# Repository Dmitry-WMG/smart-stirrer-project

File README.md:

# smart-stirrer-project
Unzip/copy this folder into the examples/ble_peripheral/ folder in the nRF SDK v.16.
Copy the stirboard.h file into components/boards folder.

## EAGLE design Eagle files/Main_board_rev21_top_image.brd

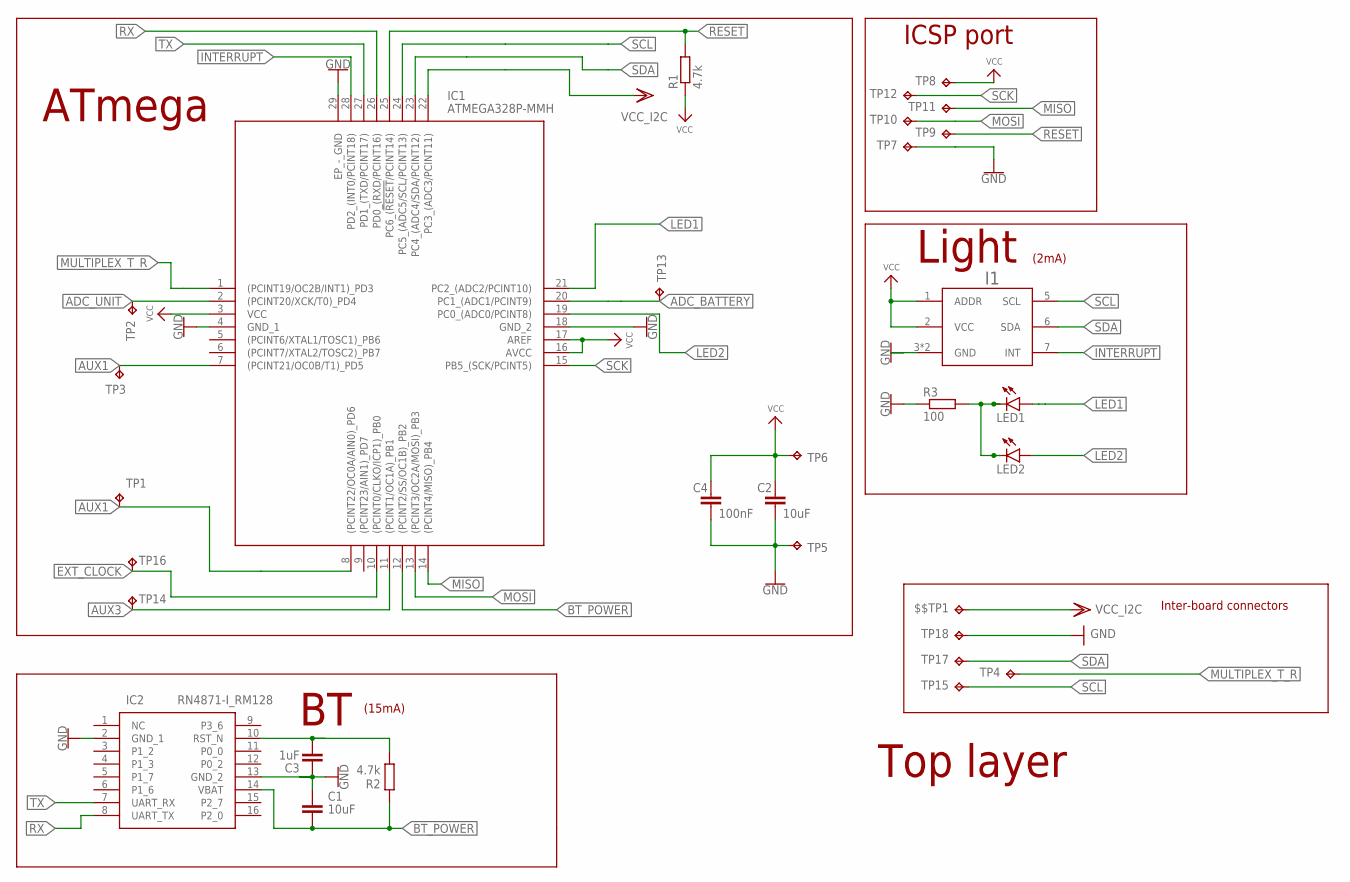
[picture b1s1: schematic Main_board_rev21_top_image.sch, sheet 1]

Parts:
$$TP1: TP; TEST_PAD_1MM
C1, C2: 10uF; C0603K
C3: 1uF; C0603K
C4: 100nF; C0603K
I1: BH1745NUC; WSON008X2120
IC1: ATMEGA328P-MMH; QFN45P400X400X100-29N
IC2: RN4871-I_RM128; RN4871
LED1, LED2: LEDCHIPLED_0603; CHIPLED_0603
R1, R2: 4.7k; R0603
R3: 100; R0603
TP1, TP2, TP3, TP4, TP5, TP6, TP13, TP14, TP15, TP16, TP17, TP18: TP; TEST_PAD_1MM
TP7, TP8, TP9, TP10, TP11, TP12: TPTP09SQ; TP09SQ

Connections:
ADC_BATTERY: IC1.20 (PC1_(ADC1/PCINT9)), TP13.P$1
ADC_UNIT: IC1.2 ((PCINT20/XCK/T0)_PD4), TP2.P$1
AUX1: IC1.7 ((PCINT21/OC0B/T1)_PD5), TP3.P$1
AUX3: IC1.11 ((PCINT1/OC1A)_PB1), TP14.P$1
BT_POWER: C1.1, IC1.12 ((PCINT2/SS/OC1B)_PB2), IC2.14 (VBAT), R2.2
BT_RESET: C3.2, IC2.10 (RST_N), R2.1
EXT_CLOCK: IC1.10 ((PCINT0/CLKO/ICP1)_PB0), TP16.P$1
GND: C1.2, C2.2, C3.1, C4.2, I1.3 (GND), I1.4 (GND), IC1.4 (GND_1), IC1.18 (GND_2), IC1.29 (EP_-_GND), IC2.2 (GND_1), IC2.13 (GND_2), R3.1, TP5.P$1, TP7.TP, TP18.P$1
INTERRUPT: I1.7 (INT), IC1.28 (PD2_(INT0/PCINT18))
LED1: IC1.21 (PC2_(ADC2/PCINT10)), LED1.A
LED2: IC1.19 (PC0_(ADC0/PCINT8)), LED2.A
MISO: IC1.14 ((PCINT4/MISO)_PB4), TP11.TP
MOSI: IC1.13 ((PCINT3/OC2A/MOSI)_PB3), TP10.TP
MULTIPLEX_T_R: IC1.1 ((PCINT19/OC2B/INT1)_PD3), TP4.P$1
unnamed: IC1.8 ((PCINT22/OC0A/AIN0)_PD6), TP1.P$1
unnamed: LED1.C, LED2.C, R3.2
RESET: IC1.25 (PC6_(!RESET!/PCINT14)), R1.2, TP9.TP
RX: IC1.26 (PD0_(RXD/PCINT16)), IC2.8 (UART_TX)
SCK: IC1.15 (PB5_(SCK/PCINT5)), TP12.TP
SCL: I1.5 (SCL), IC1.24 (PC5_(ADC5/SCL/PCINT13)), TP15.P$1
SDA: I1.6 (SDA), IC1.23 (PC4_(ADC4/SDA/PCINT12)), TP17.P$1
TX: IC1.27 (PD1_(TXD/PCINT17)), IC2.7 (UART_RX)
VCC: C2.1, C4.1, I1.1 (ADDR), I1.2 (VCC), IC1.3 (VCC), IC1.16 (AVCC), IC1.17 (AREF), R1.1, TP6.P$1, TP8.TP
VDD: $$TP1.P$1, IC1.22 (PC3_(ADC3/PCINT11))

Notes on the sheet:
ICSP port
Light
ATmega
(2mA)
(15mA)
Top layer
Inter-board connectors

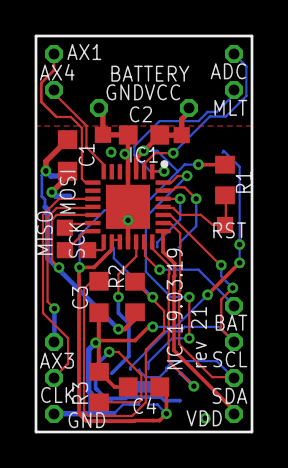
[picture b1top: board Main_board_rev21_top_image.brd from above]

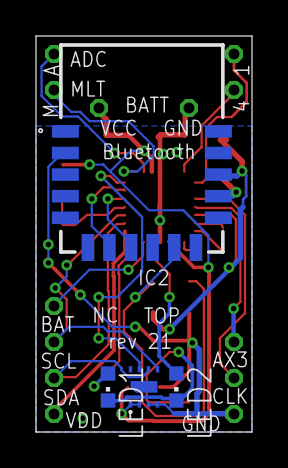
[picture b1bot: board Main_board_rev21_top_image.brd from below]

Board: 2 copper layers, 12.0 x 22.0 mm, 31 parts (4 on the bottom side), 24 nets.

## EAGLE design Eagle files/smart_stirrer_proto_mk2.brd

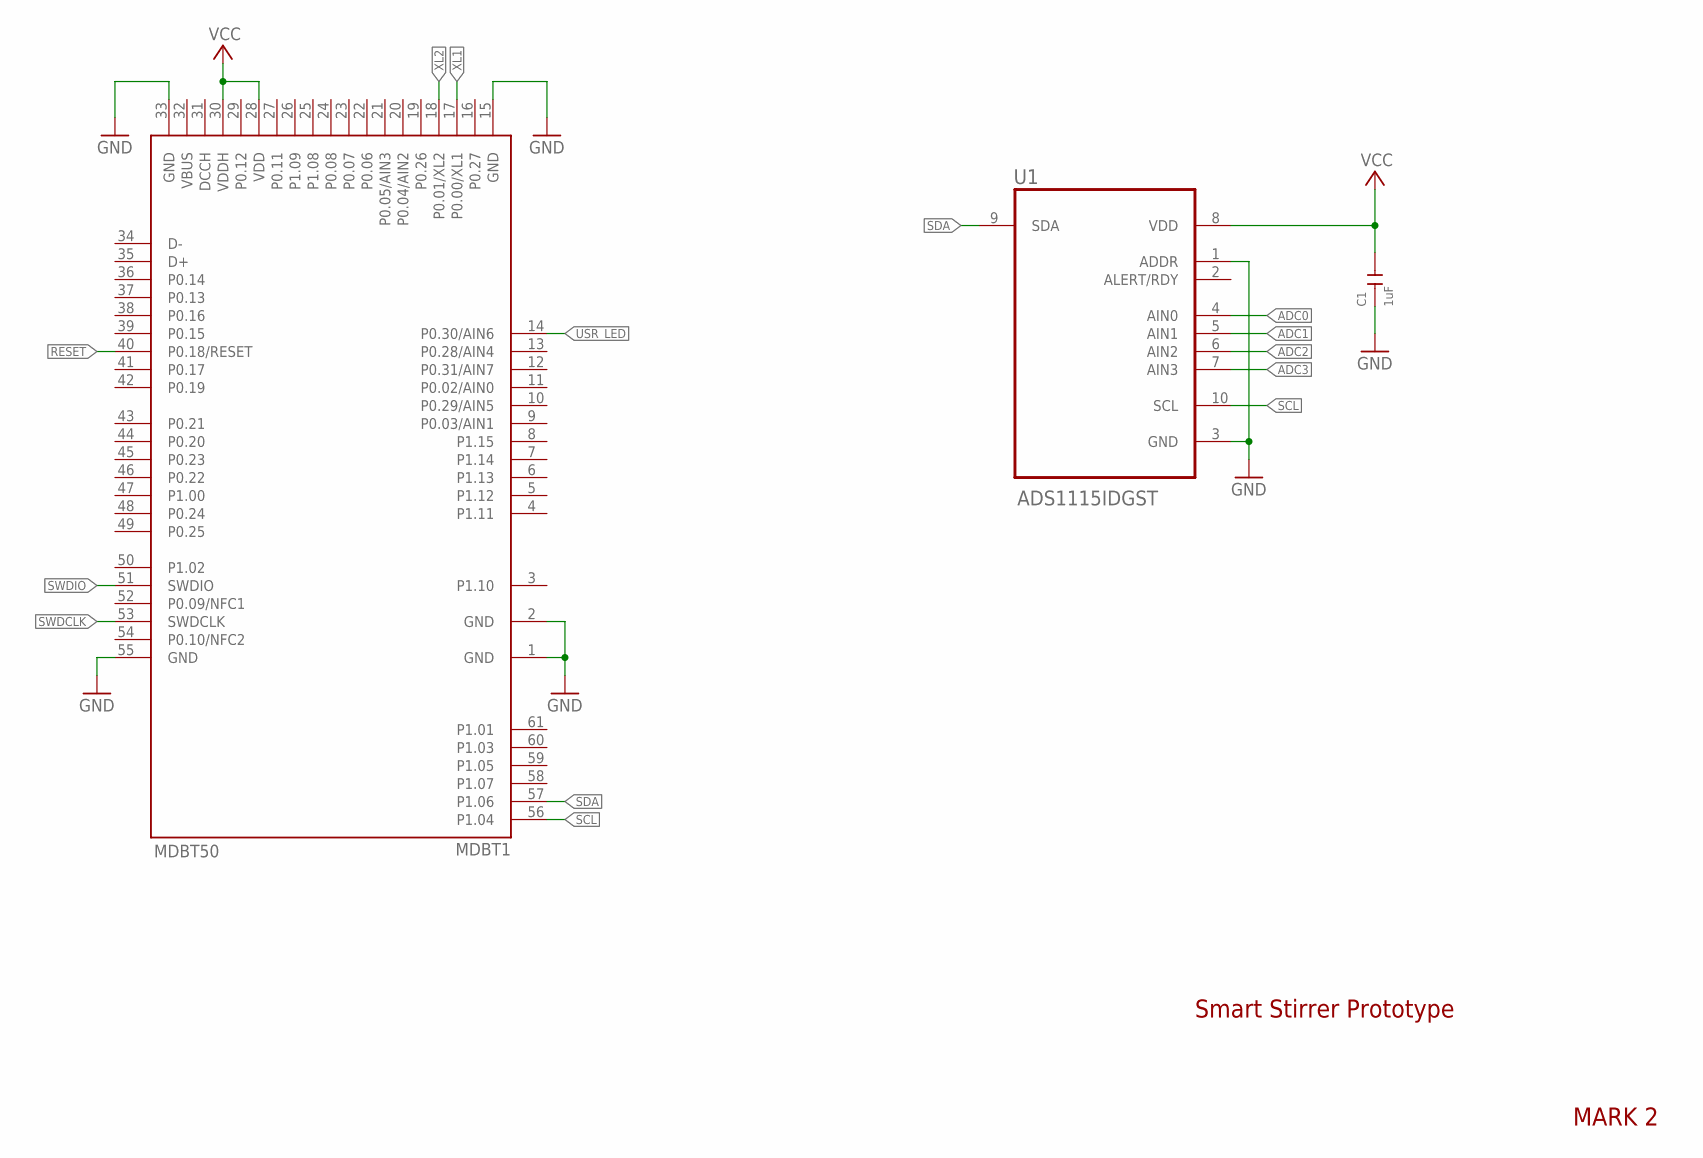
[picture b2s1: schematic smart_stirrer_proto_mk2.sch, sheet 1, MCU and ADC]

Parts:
C1: 1uF; C0402
MDBT1: MDBT50
U1: ADS1115IDGST; SOP50P490X110-10N

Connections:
ADC0: U1.4 (AIN0); also elsewhere on the board
ADC1: U1.5 (AIN1); also elsewhere on the board
ADC2: U1.6 (AIN2); also elsewhere on the board
ADC3: U1.7 (AIN3)
GND: C1.1, MDBT1.1 (GND), MDBT1.2 (GND), MDBT1.15 (GND), MDBT1.33 (GND), MDBT1.55 (GND), U1.1 (ADDR), U1.3 (GND); also elsewhere on the board
RESET: MDBT1.40 (P0.18/RESET); also elsewhere on the board
SCL: MDBT1.56 (P1.04), U1.10 (SCL); also elsewhere on the board
SDA: MDBT1.57 (P1.06), U1.9 (SDA); also elsewhere on the board
SWDCLK: MDBT1.53 (SWDCLK); also elsewhere on the board
SWDIO: MDBT1.51 (SWDIO); also elsewhere on the board
USR_LED: MDBT1.14 (P0.30/AIN6); also elsewhere on the board
VCC: C1.2, MDBT1.28 (VDD), MDBT1.30 (VDDH), U1.8 (VDD); also elsewhere on the board
XL1: MDBT1.17 (P0.00/XL1); also elsewhere on the board
XL2: MDBT1.18 (P0.01/XL2); also elsewhere on the board

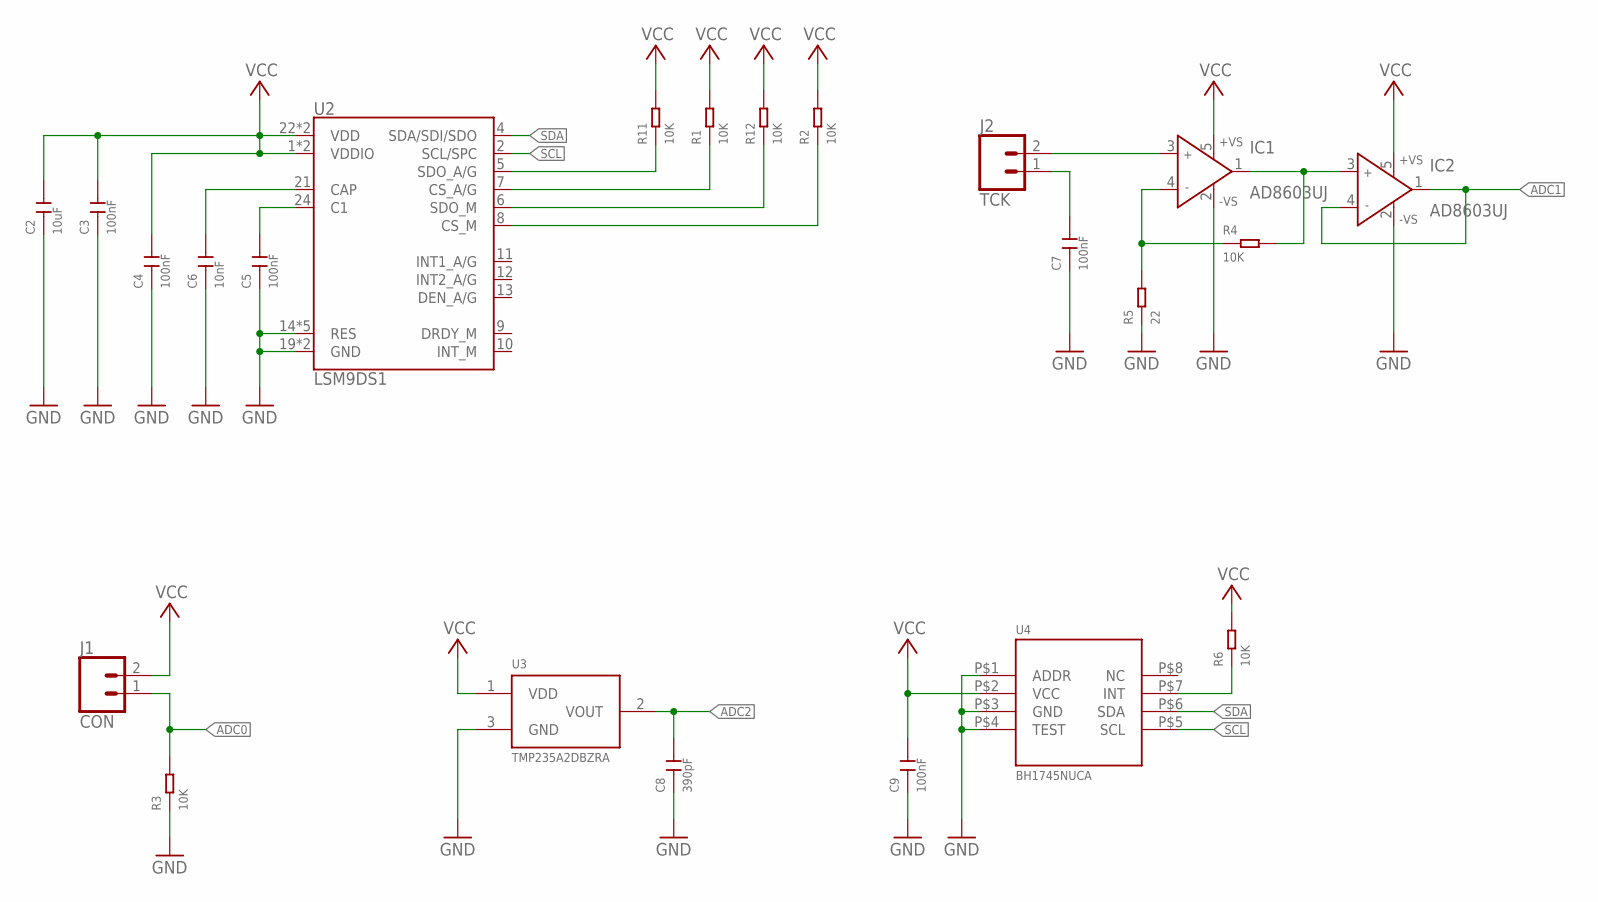
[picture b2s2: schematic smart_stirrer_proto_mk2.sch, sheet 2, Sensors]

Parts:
C2: 10uF; C0402
C3, C4, C5, C7, C9: 100nF; C0402
C6: 10nF; C0402
C8: 390pF; C0402
IC1, IC2: AD8603UJ; SOT23-5
J1: CON; 1X02_NO_SILK
J2: TCK; 1X02_NO_SILK
R1, R2, R3, R4, R6, R11, R12: 10K; R0402
R5: 22; R0402
U2: LSM9DS1; LGA24-8X4
U3: TMP235A2DBZRA; SOT-23-3
U4: BH1745NUCA; BH1745NUC-E2

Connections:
ADC0: J1.1, R3.2; also elsewhere on the board
ADC1: IC2.1 (OUT), IC2.4 (IN-); also elsewhere on the board
ADC2: C8.2, U3.2 (VOUT); also elsewhere on the board
GND: C2.1, C3.1, C4.1, C5.1, C6.1, C7.1, C8.1, C9.1, IC1.2 (-VS), IC2.2 (-VS), R3.1, R5.1, U2.14 (RES), U2.15 (RES), U2.16 (RES), U2.17 (RES), U2.18 (RES), U2.19 (GND), U2.20 (GND), U3.3 (GND), U4.P$1 (ADDR), U4.P$3 (GND), U4.P$4 (TEST); also elsewhere on the board
unnamed: C5.2, U2.24 (C1)
unnamed: C6.2, U2.21 (CAP)
unnamed: IC1.1 (OUT), IC2.3 (IN+), R4.2
unnamed: R1.1, U2.7 (CS_A/G)
unnamed: R2.1, U2.8 (CS_M)
unnamed: IC1.3 (IN+), J2.2
unnamed: IC1.4 (IN-), R4.1, R5.2
unnamed: C7.2, J2.1
unnamed: R6.1, U4.P$7 (INT)
unnamed: R11.1, U2.5 (SDO_A/G)
unnamed: R12.1, U2.6 (SDO_M)
SCL: U2.2 (SCL/SPC), U4.P$5 (SCL); also elsewhere on the board
SDA: U2.4 (SDA/SDI/SDO), U4.P$6 (SDA); also elsewhere on the board
VCC: C2.2, C3.2, C4.2, C9.2, IC1.5 (+VS), IC2.5 (+VS), J1.2, R1.2, R2.2, R6.2, R11.2, R12.2, U2.1 (VDDIO), U2.3 (VDDIO), U2.22 (VDD), U2.23 (VDD), U3.1 (VDD), U4.P$2 (VCC); also elsewhere on the board

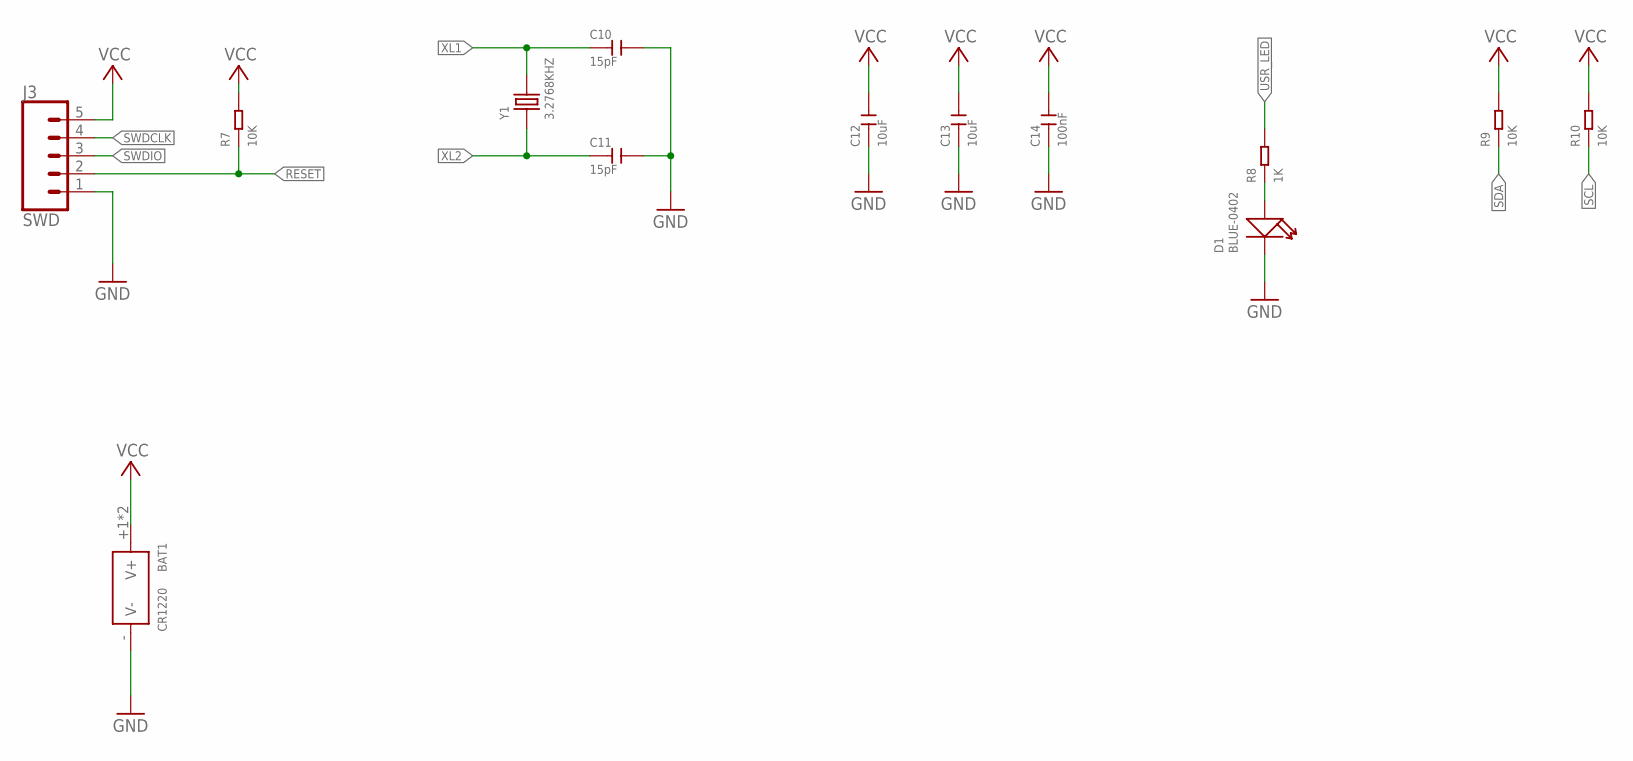
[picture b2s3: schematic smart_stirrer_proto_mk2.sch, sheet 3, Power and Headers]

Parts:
BAT1: CR1220; BAT2P-13.5-CR1220
C10, C11: 15pF; C0402
C12, C13: 10uF; C0402
C14: 100nF; C0402
D1: BLUE-0402; LED-0402
J3: SWD; 1X05_NO_SILK
R7, R9, R10: 10K; R0402
R8: 1K; R0402
Y1: 3.2768KHZ; X2-SMD-L2.0X1.2X0.55MM

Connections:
GND: BAT1.- (V-), C10.2, C11.2, C12.1, C13.1, C14.1, D1.-, J3.1; also elsewhere on the board
unnamed: D1.+, R8.1
RESET: J3.2, R7.1; also elsewhere on the board
SCL: R10.1; also elsewhere on the board
SDA: R9.1; also elsewhere on the board
SWDCLK: J3.4; also elsewhere on the board
SWDIO: J3.3; also elsewhere on the board
USR_LED: R8.2; also elsewhere on the board
VCC: BAT1.+1 (V+), BAT1.+2 (V+), C12.2, C13.2, C14.2, J3.5, R7.2, R9.2, R10.2; also elsewhere on the board
XL1: C10.1, Y1.2; also elsewhere on the board
XL2: C11.1, Y1.1; also elsewhere on the board

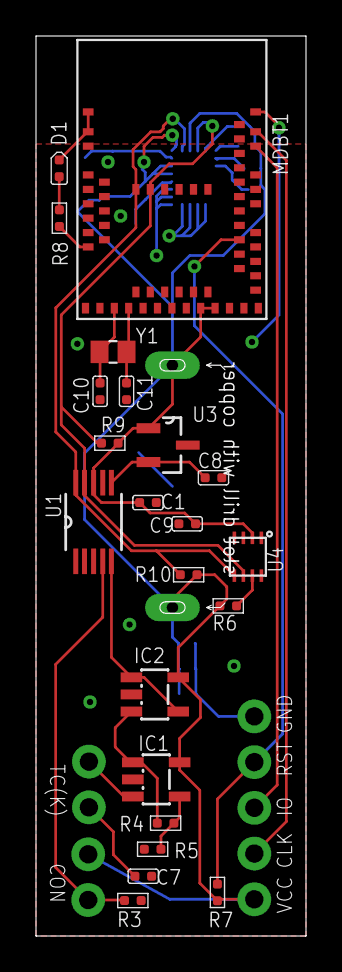
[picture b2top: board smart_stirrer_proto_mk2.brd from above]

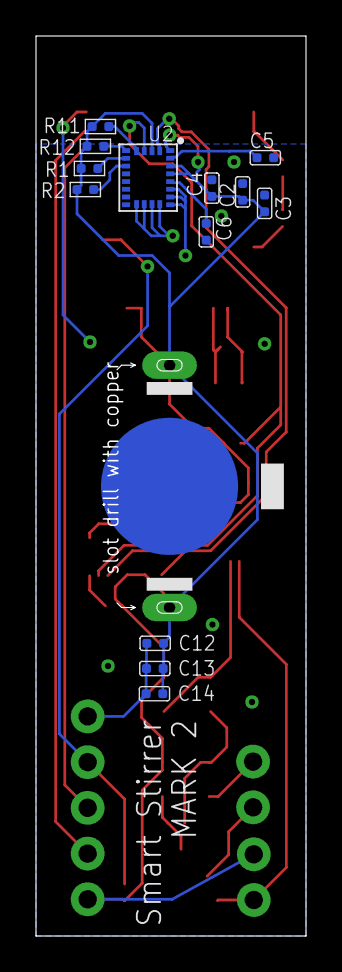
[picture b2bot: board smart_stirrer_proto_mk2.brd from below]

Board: 2 copper layers, 15.0 x 50.0 mm, 39 parts (14 on the bottom side), 25 nets.

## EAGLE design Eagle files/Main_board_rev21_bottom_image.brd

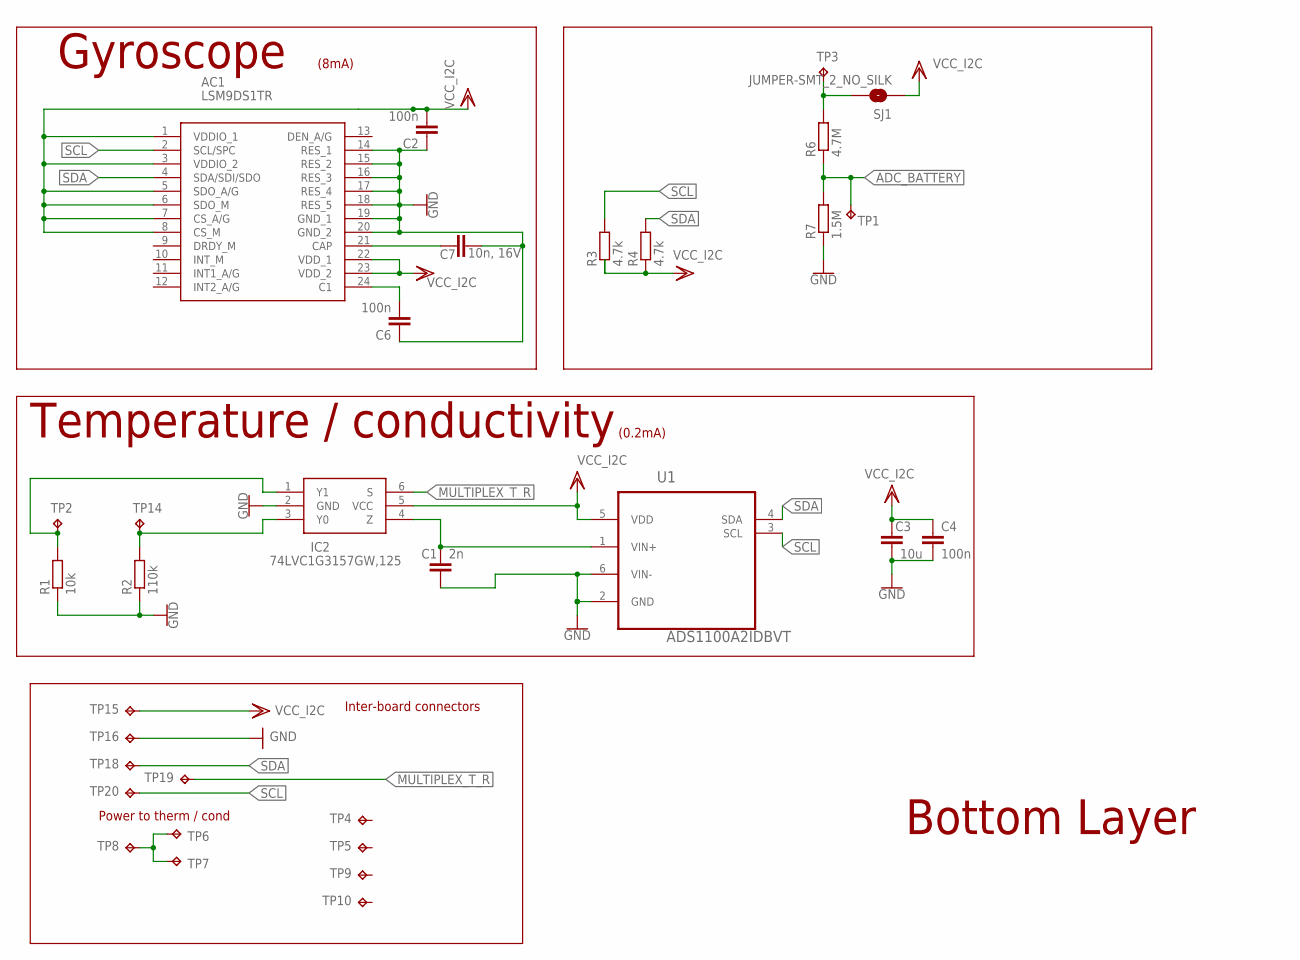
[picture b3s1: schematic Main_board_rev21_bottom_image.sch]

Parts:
AC1: LSM9DS1TR; LGA-24L(3X3.5X1MM)
C1: 2n; C0603K
C2, C4, C6: 100n; C0603K
C3: 10u; C0603K
C7: 10n, 16V; C0603K
IC2: 74LVC1G3157GW,125; SOT65P210X110-6N
R1: 10k; R0603
R2: 110k; R0603
R3, R4: 4.7k; R0603
R6: 4.7M; R0603
R7: 1.5M; R0603
SJ1: JUMPER-SMT_2_NO_SILK; SMT-JUMPER_2_NO_SILK
TP1, TP2, TP3, TP4, TP5, TP6, TP7, TP8, TP9, TP10, TP14, TP15, TP16, TP18, TP19, TP20: TP; TEST_PAD_1MM
U1: ADS1100A2IDBVT; SOT95P280X145-6N

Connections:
ADC_BATTERY: R6.1, R7.2, TP1.P$1
COND: IC2.1 (Y1), R1.2, TP2.P$1
GND: AC1.14 (RES_1), AC1.15 (RES_2), AC1.16 (RES_3), AC1.17 (RES_4), AC1.18 (RES_5), AC1.19 (GND_1), AC1.20 (GND_2), C1.2, C2.1, C3.1, C4.2, C6.1, C7.2, IC2.2 (GND), R1.1, R2.1, R7.1, TP16.P$1, U1.2 (GND), U1.6 (VIN-)
MULTIPLEX_T_R: IC2.6 (S), TP19.P$1
unnamed: C1.1, IC2.4 (Z), U1.1 (VIN+)
unnamed: TP6.P$1, TP7.P$1, TP8.P$1
unnamed: R6.2, SJ1.2, TP3.P$1
unnamed: AC1.21 (CAP), C7.1
unnamed: AC1.24 (C1), C6.2
SCL: AC1.2 (SCL/SPC), R3.2, TP20.P$1, U1.3 (SCL)
SDA: AC1.4 (SDA/SDI/SDO), R4.2, TP18.P$1, U1.4 (SDA)
THERM: IC2.3 (Y0), R2.2, TP14.P$1
VDD: AC1.1 (VDDIO_1), AC1.3 (VDDIO_2), AC1.5 (SDO_A/G), AC1.6 (SDO_M), AC1.7 (CS_A/G), AC1.8 (CS_M), AC1.22 (VDD_1), AC1.23 (VDD_2), C2.2, C3.2, C4.1, IC2.5 (VCC), R3.1, R4.1, SJ1.1, TP15.P$1, U1.5 (VDD)

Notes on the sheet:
Temperature / conductivity
Gyroscope
(8mA)
(0.2mA)
Bottom Layer
Inter-board connectors
Power to therm / cond

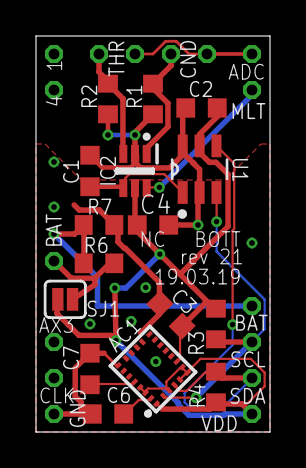
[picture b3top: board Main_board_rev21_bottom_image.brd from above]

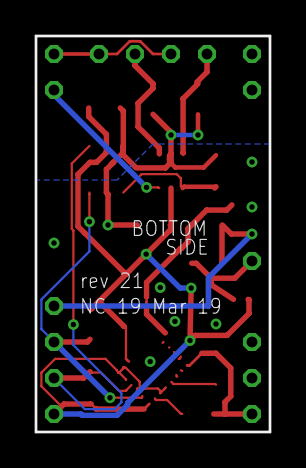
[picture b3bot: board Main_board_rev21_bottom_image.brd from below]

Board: 2 copper layers, 13.0 x 22.0 mm, 32 parts (2 on the bottom side), 13 nets.

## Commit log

2020-04-05 Add files via upload
    These are Segger files for a flash of Smart Stirrer nordic board.
2020-04-05 Add files via upload
    Segger files to flash the Smart Stirrer for inertia sensor. Unzip this into the examples/ble_peripheral/ folder in the nRF SDK. Copy the stirboard.h file into components/boards folder. Make sure ther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
    #elif defined(BOARD_STIRBOARD)
    #include "stirboard.h"
2020-04-08 Add files via upload
    Files for Arduino version of the Smart Stirrer
2020-06-11 Add files via upload
    The python scripts for reading the data from Smart Stirrer.

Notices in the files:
parts and their libraries:
SparkFun-Jumpers: Licensing: Creative Commons ShareAlike 4.0 International - https://creativecommons.org/licenses/by-sa/4.0
